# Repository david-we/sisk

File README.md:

# SiSK 

**THIS IS STILL WORK IN PROGRESS !**  

SiSK is a split keyboard with focus on standard staggered ISO Layout. it is an opportunity for those that do not want to jump on the ortholinear bandwagon, but still want to have the ergonomic advantages of a split keyboard. There will be a 60% version and a 65% Version of the PCB (which is already in the making). 

The plan is it starts as a base PCB which can then be easily used for DIY 3D-printed case designs. I am also planing to experiment with different case mounting techniques like top mount, sandwich mount, tray mount, gasket mount...

SiSK is meant as a wireless keyboard and my first prototype will use nice!nano v2 compatible Microcontroller boards and el cheapo 128x32 i2C displays for monitoring the battery...

## naming
**S**plit **I**SO **S**taggered **K**eyboard  
i know very ingenious :sweat_smile: but it was a very quick decision and AI created a logo that i liked, so its fine!

## features

- split
- ISO
- staggered
- wireless
- screw on wrist/palm wrest
- 128x32 OLED Display (I2C)
- 60% and 65% Version available
- first case will probably also use a foldable tenting solution (chinese mini Laptop stands)

### why?

I know there are similar keyboards out there, in fact there are also kits available that are in the same category. But still i was not satisfied with the existing solutions. Some where also hard to get in europe or had no ISO Layout. Another big point for me was the learning aspect, especially KiCAD and SMD soldering. AND i want a detachable solution for palm rests.

## pics

### history

last year i made this thing, which is kind of the predecessor of SiSK. But handwired and driven by a raspberry pi pico. It worked very well but the connector between the two halves sometimes looses contact. then i have to wobble around on the connector and it works again :P ... otherwise it worked flawless  

## next steps

waiting for PCBs :) 

## ideas for future

- ANSI layout

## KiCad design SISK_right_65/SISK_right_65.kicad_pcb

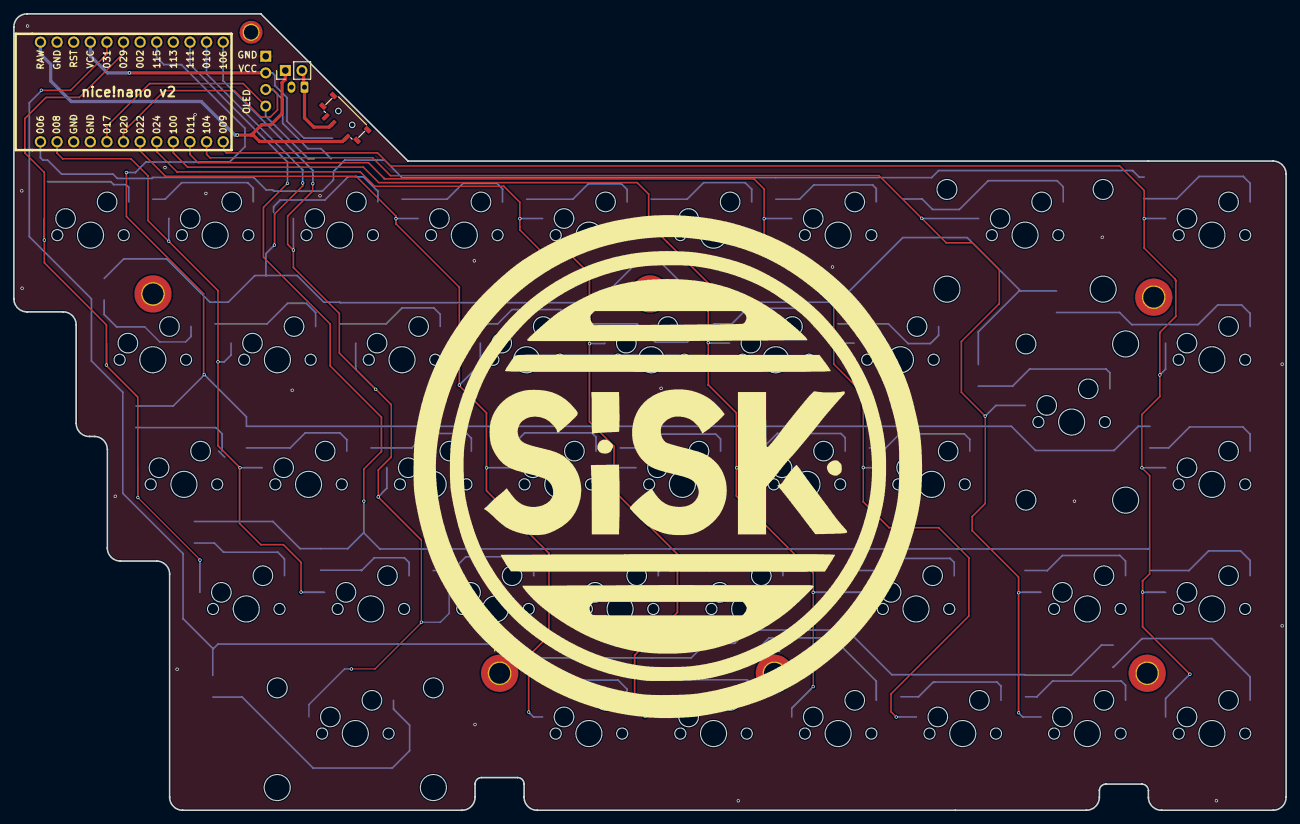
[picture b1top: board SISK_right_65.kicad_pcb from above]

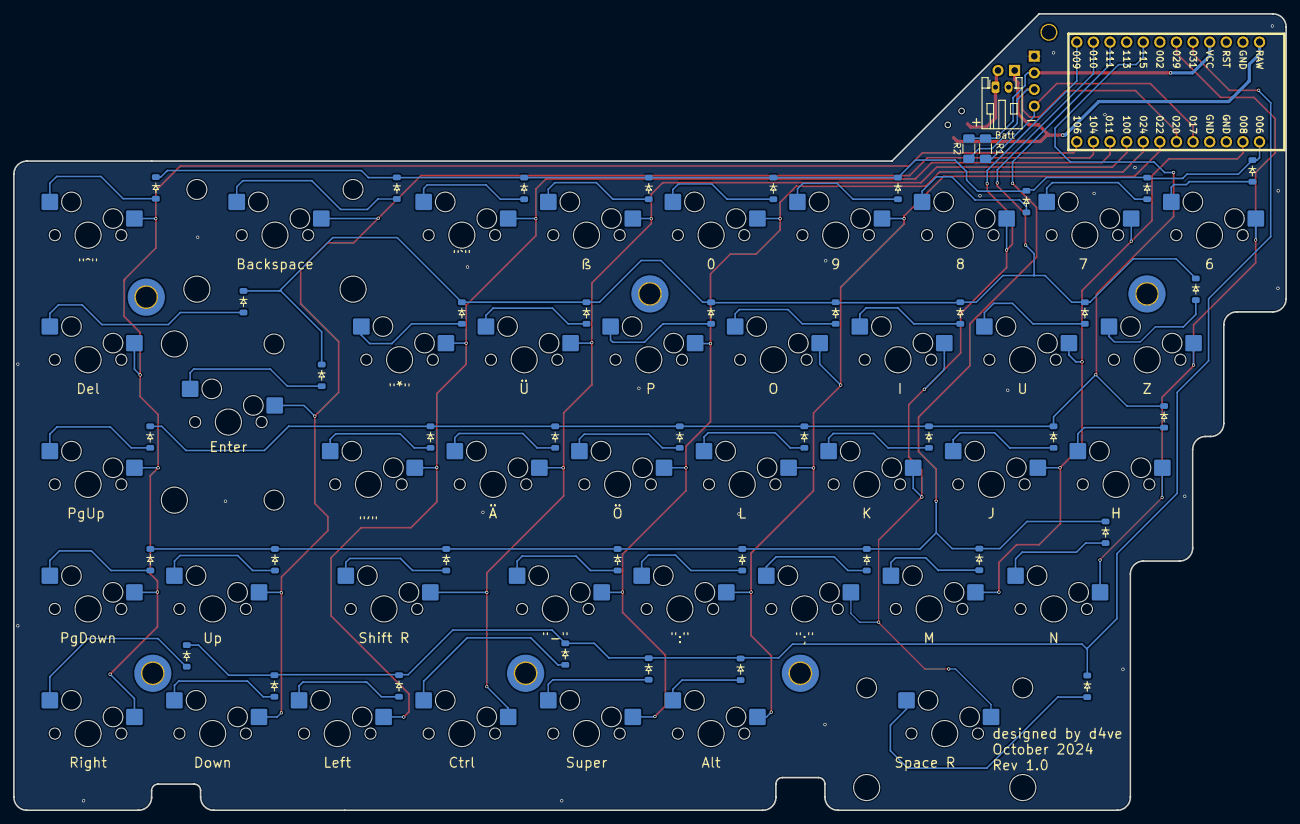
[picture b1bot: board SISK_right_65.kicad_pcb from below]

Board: 2 copper layers, 194.5 x 121.8 mm, 96 parts (85 on the bottom side), 61 nets.

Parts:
D1, D2, D3, D4, D5, D6, D7, D8, D9, D10, D11, D12, D13, D15, D16, D17, D18, D19, D21, D22, D23, D24, D25, D26, D27, D28, D29, D30, D31, D32, D33, D34, D35, D36, D37, D38, D39, D41, D42, D43, D44: D; Diode_SOD-123
H1, H2, H3, H4, H5, H7: M3; MountingHole_3.2mm_M3_ISO7380_Pad_TopBottom
H6: M2; MountingHole_2.2mm_M2_ISO7380_Pad_TopOnly
J1: OLED_128x32
J2: Batt; JST_PH_S2B-PH-K_1x02_P2.00mm_Horizontal
J3: SWITCH; PinHeader_1x02_P2.54mm_Vertical
R1, R2: 5K; R_1206_3216Metric_Pad1.30x1.75mm_HandSolder
SW1, SW2, SW3, SW4, SW5, SW6, SW7, SW9, SW10, SW11, SW12, SW13, SW14, SW15, SW16, SW18, SW19, SW20, SW21, SW22, SW23, SW24, SW25, SW26, SW27, SW28, SW29, SW30, SW31, SW33, SW34, SW36, SW37, SW38, SW39, SW40, SW41: SW_push; MX-Hotswap-1U
SW8: SW_push; MX-Hotswap-2U
SW17: SW_push; MX-Hotswap-ISO
SW32: SW_push; MX-Hotswap-1.75U
SW35: SW_push; MX-Hotswap-2.75U
SW-ONOFF-01: Switch_MSK12C02
U1: Nice_Nano_V2; nice_nano

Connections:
+3,3V: J1.2 (VCC), R1.1, R2.1, U1.21 (3.3v)
+BATT: J2.1, J3.2, SW-ONOFF-01.2 (B)
+VDC: J3.1, SW-ONOFF-01.1 (A), U1.24 (B+)
/COL0: SW1.1, SW10.1, SW19.1, SW27.1, U1.19 (20)
/COL1: SW2.1, SW11.1, SW20.1, SW28.1, U1.2 (0)
/COL2: SW3.1, SW12.1, SW21.1, SW29.1, SW35.1, U1.13 (10)
/COL3: SW4.1, SW13.1, SW22.1, SW30.1, SW36.1, U1.7 (4)
/COL4: SW5.1, SW14.1, SW23.1, SW31.1, SW37.1, U1.8 (5)
/COL5: SW6.1, SW15.1, SW24.1, SW32.1, SW38.1, U1.9 (6)
/COL6: SW7.1, SW16.1, SW25.1, SW39.1, U1.10 (7)
/COL7: SW8.1, SW17.1, SW33.1, SW40.1, U1.11 (8)
/COL8: SW9.1, SW18.1, SW26.1, SW34.1, SW41.1, U1.12 (9)
/ROW0: D1.1 (K), D6.1 (K), D11.1 (K), D16.1 (K), D21.1 (K), D26.1 (K), D31.1 (K), D36.1 (K), D41.1 (K), U1.1
/ROW1: D2.1 (K), D7.1 (K), D12.1 (K), D17.1 (K), D22.1 (K), D27.1 (K), D32.1 (K), D37.1 (K), D42.1 (K), U1.14 (16)
/ROW2: D3.1 (K), D13.1 (K), D18.1 (K), D23.1 (K), D28.1 (K), D33.1 (K), D38.1 (K), D43.1 (K), U1.17 (18)
/ROW3: D4.1 (K), D9.1 (K), D19.1 (K), D24.1 (K), D29.1 (K), D34.1 (K), D39.1 (K), D44.1 (K), U1.15 (14)
/ROW4: D5.1 (K), D8.1 (K), D10.1 (K), D15.1 (K), D25.1 (K), D30.1 (K), D35.1 (K), U1.20 (21)
/SCL: J1.3 (SCL), R2.2, U1.6 (3)
/SDA: J1.4 (SDA), R1.2, U1.5 (2)
GND: J1.1 (GND), J2.2, U1.3 (GND), U1.4 (GND), U1.23 (GND)
unnamed: D1.2 (A), SW9.2
unnamed: D2.2 (A), SW18.2
unnamed: D3.2 (A), SW26.2
unnamed: D4.2 (A), SW34.2
unnamed: D5.2 (A), SW41.2
unnamed: D6.2 (A), SW8.2
unnamed: D7.2 (A), SW17.2
unnamed: D8.2 (A), SW35.2
unnamed: D9.2 (A), SW33.2
unnamed: D10.2 (A), SW40.2
unnamed: D11.2 (A), SW7.2
unnamed: D12.2 (A), SW16.2
unnamed: D13.2 (A), SW25.2
unnamed: D15.2 (A), SW39.2
unnamed: D16.2 (A), SW6.2
unnamed: D17.2 (A), SW15.2
unnamed: D18.2 (A), SW24.2
unnamed: D19.2 (A), SW32.2
unnamed: D21.2 (A), SW5.2
unnamed: D22.2 (A), SW14.2
unnamed: D23.2 (A), SW23.2
unnamed: D24.2 (A), SW31.2
unnamed: D25.2 (A), SW38.2
unnamed: D26.2 (A), SW4.2
unnamed: D27.2 (A), SW13.2
unnamed: D28.2 (A), SW22.2
unnamed: D29.2 (A), SW30.2
unnamed: D30.2 (A), SW37.2
unnamed: D31.2 (A), SW3.2
unnamed: D32.2 (A), SW12.2
unnamed: D33.2 (A), SW21.2
unnamed: D34.2 (A), SW29.2
unnamed: D35.2 (A), SW36.2
unnamed: D36.2 (A), SW2.2
unnamed: D37.2 (A), SW11.2
unnamed: D38.2 (A), SW20.2
unnamed: D39.2 (A), SW28.2
unnamed: D41.2 (A), SW1.2
unnamed: D42.2 (A), SW10.2
unnamed: D43.2 (A), SW19.2
unnamed: D44.2 (A), SW27.2

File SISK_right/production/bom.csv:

Designator,Footprint,Quantity,Value,LCSC Part #
"D1, D10, D11, D12, D13, D15, D16, D17, D18, D19, D2, D21, D22, D23, D24, D25, D26, D27, D28, D29, D3, D30, D31, D32, D33, D34, D35, D36, D37, D38, D39, D4, D41, D42, D43, D44, D5, D6, D7, D8, D9",Diode_SOD-123,41,D,
J1,OLED_128x32,1,OLED_128x32,
J2,JST_PH_S2B-PH-K_1x02_P2.00mm_Horizontal,1,Battery Connector,
SW-ONOFF-01,Switch_MSK12C02,1,~,
SW1,Hotswap_MX_Plated_1.00u,1,"""6""",
SW10,Hotswap_MX_Plated_1.00u,1,"""Z""",
SW11,Hotswap_MX_Plated_1.00u,1,"""U""",
SW12,Hotswap_MX_Plated_1.00u,1,"""I""",
SW13,Hotswap_MX_Plated_1.00u,1,"""O""",
SW14,Hotswap_MX_Plated_1.00u,1,"""P""",
SW15,Hotswap_MX_Plated_1.00u,1,"""Ü""",
SW16,Hotswap_MX_Plated_1.00u,1,"""*""",
SW17,Hotswap_MX_Plated_ISOEnter,1,"""Enter""",
SW18,Hotswap_MX_Plated_1.00u,1,"""Del""",
SW19,Hotswap_MX_Plated_1.00u,1,"""H""",
SW2,Hotswap_MX_Plated_1.00u,1,"""7""",
SW20,Hotswap_MX_Plated_1.00u,1,"""J""",
SW21,Hotswap_MX_Plated_1.00u,1,"""K""",
SW22,Hotswap_MX_Plated_1.00u,1,"""L""",
SW23,Hotswap_MX_Plated_1.00u,1,"""Ö""",
SW24,Hotswap_MX_Plated_1.00u,1,"""Ä""",
SW25,Hotswap_MX_Plated_1.00u,1,"""'""",
SW26,Hotswap_MX_Plated_1.00u,1,"""PGUP""",
SW27,Hotswap_MX_Plated_1.00u,1,"""N""",
SW28,Hotswap_MX_Plated_1.00u,1,"""M""",
SW29,Hotswap_MX_Plated_1.00u,1,""";""",
SW3,Hotswap_MX_Plated_1.00u,1,"""8""",
SW30,Hotswap_MX_Plated_1.00u,1,""":""",
SW31,Hotswap_MX_Plated_1.00u,1,"""-""",
SW32,Hotswap_MX_Plated_1.75u,1,"""shift_R""",
SW33,Hotswap_MX_Plated_1.00u,1,"""UP""",
SW34,Hotswap_MX_Plated_1.00u,1,"""PGDOWN""",
SW35,Hotswap_MX_Plated_2.75u,1,"""SPACE_R""",
SW36,Hotswap_MX_Plated_1.00u,1,"""Alt""",
SW37,Hotswap_MX_Plated_1.00u,1,FN,
SW38,Hotswap_MX_Plated_1.00u,1,"""Ctrl""",
SW39,Hotswap_MX_Plated_1.00u,1,"""Left""",
SW4,Hotswap_MX_Plated_1.00u,1,"""9""",
SW40,Hotswap_MX_Plated_1.00u,1,"""Down""",
SW41,Hotswap_MX_Plated_1.00u,1,"""Right""",
SW5,Hotswap_MX_Plated_1.00u,1,"""0""",
SW6,Hotswap_MX_Plated_1.00u,1,"""ß""",
SW7,Hotswap_MX_Plated_1.00u,1,"""`""",
SW8,Hotswap_MX_Plated_2.00u,1,"""Backspace""",
SW9,Hotswap_MX_Plated_1.00u,1,"""^""",
U1,Nice_Nano_V2,1,Nice_Nano_V2,

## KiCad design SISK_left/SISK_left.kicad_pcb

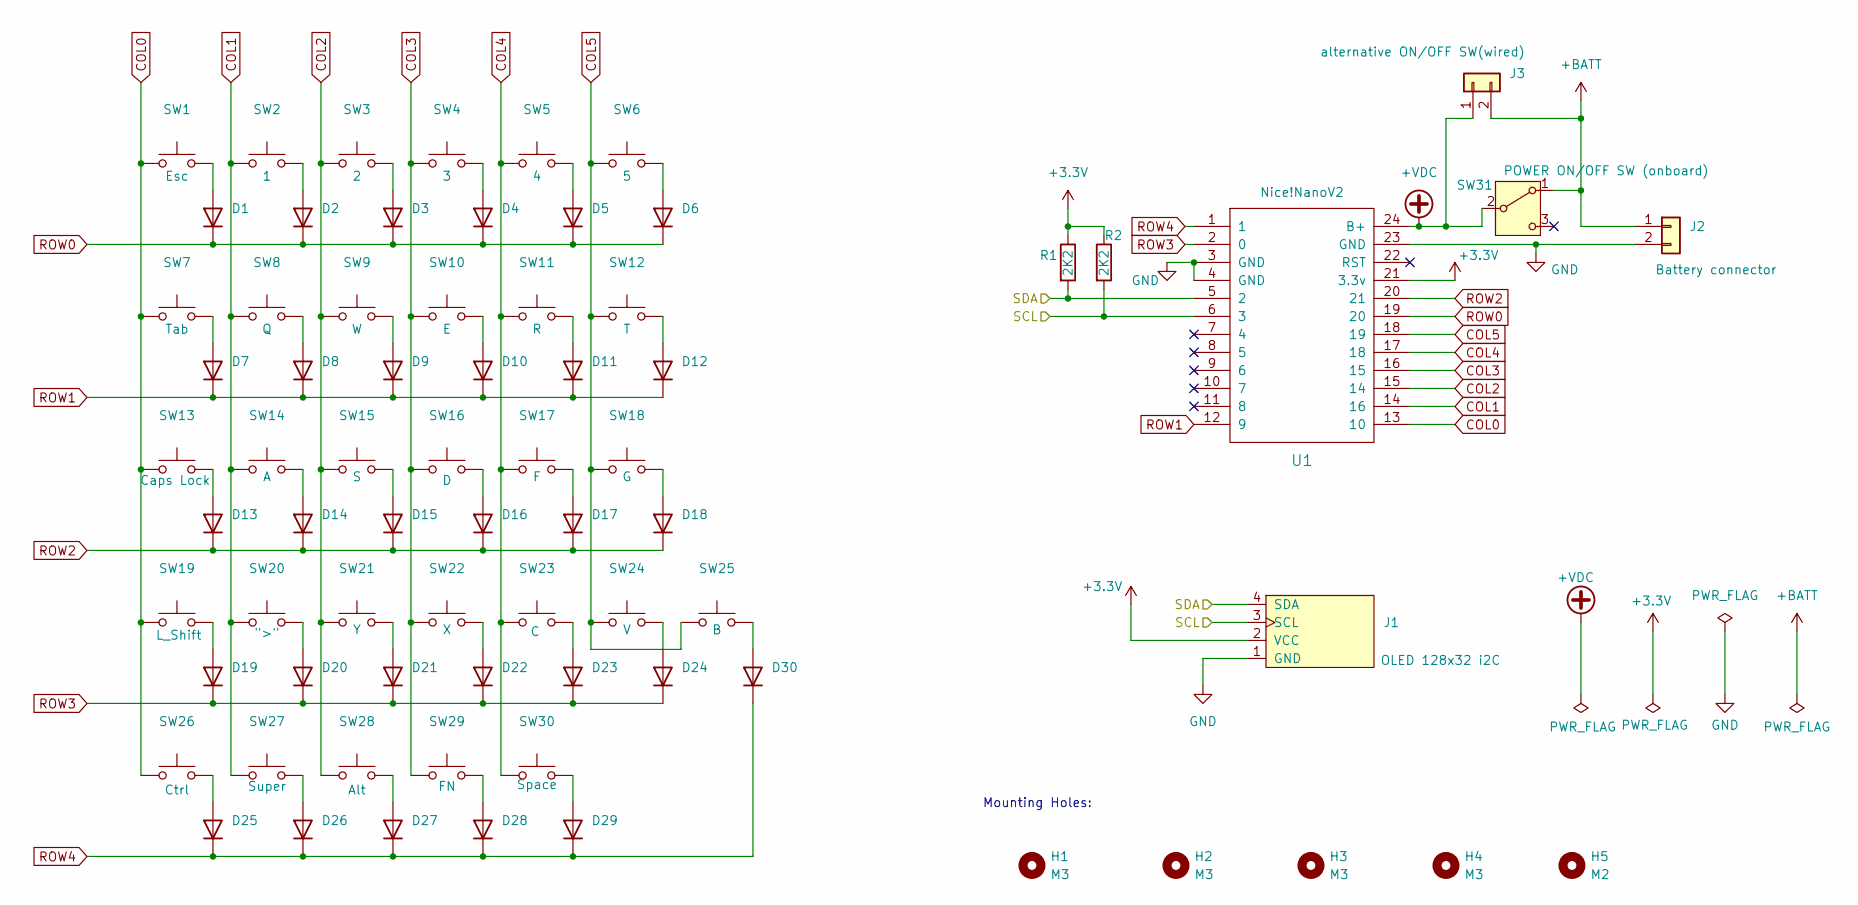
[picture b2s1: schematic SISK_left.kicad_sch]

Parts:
D1, D2, D3, D4, D5, D6, D7, D8, D9, D10, D11, D12, D13, D14, D15, D16, D17, D18, D19, D20, D21, D22, D23, D24, D25, D26, D27, D28, D29, D30: 1n4148; Diode_SOD-123; MPN 1N4148W
H1, H2, H3, H4: M3; MountingHole_3.2mm_M3_ISO7380_Pad_TopBottom
H5: M2; MountingHole_2.2mm_M2_ISO7380_Pad_TopOnly
J1: OLED_128x32; MPN OLED 128x32 i2C
J2: BAT; JST_PH_S2B-PH-K_1x02_P2.00mm_Horizontal; MPN S2B-PH-K-S(LF)(SN)
J3: CONN_ALT; PinHeader_1x02_P2.54mm_Vertical; MPN not known yet
R1, R2: 2K2; R_1206_3216Metric_Pad1.30x1.75mm_HandSolder; MPN RC1206JR-072K2L
SW1, SW2, SW3, SW4, SW5, SW6, SW8, SW9, SW10, SW11, SW12, SW14, SW15, SW16, SW17, SW18, SW20, SW21, SW22, SW23, SW24, SW25: SW_push; MX-Hotswap-1U; MPN CPG151101S11
SW7: SW_push; MX-Hotswap-1.5U; MPN CPG151101S11
SW13: SW_push; MX-Hotswap-1.75U; MPN CPG151101S11
SW19, SW26, SW27, SW28, SW29: SW_push; MX-Hotswap-1.25U; MPN CPG151101S11
SW30: SW_push; MX-Hotswap-2.25U; MPN CPG151101S11
SW31: SW_SPDT; Switch_MSK12C02; MPN MSK12C01
U1: Nice_Nano_V2; nice_nano; MPN nice!nano v2 or compatible

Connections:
+3.3V: J1.2 (VCC), R1.1, R2.1, U1.21 (3.3v)
+BATT: J2.1, J3.2, SW31.1 (A)
+VDC: J3.1, SW31.2 (B), U1.24 (B+)
/SCL: J1.3 (SCL), R2.2, U1.6 (3)
/SDA: J1.4 (SDA), R1.2, U1.5 (2)
COL0: SW1.1, SW7.1, SW13.1, SW19.1, SW26.1, U1.13 (10)
COL1: SW2.1, SW8.1, SW14.1, SW20.1, SW27.1, U1.14 (16)
COL2: SW3.1, SW9.1, SW15.1, SW21.1, SW28.1, U1.15 (14)
COL3: SW4.1, SW10.1, SW16.1, SW22.1, SW29.1, U1.16 (15)
COL4: SW5.1, SW11.1, SW17.1, SW23.1, SW30.1, U1.17 (18)
COL5: SW6.1, SW12.1, SW18.1, SW24.1, SW25.1, U1.18 (19)
GND: J1.1 (GND), J2.2, U1.3 (GND), U1.4 (GND), U1.23 (GND)
unnamed: D1.2 (A), SW1.2
unnamed: D2.2 (A), SW2.2
unnamed: D3.2 (A), SW3.2
unnamed: D4.2 (A), SW4.2
unnamed: D5.2 (A), SW5.2
unnamed: D6.2 (A), SW6.2
unnamed: D7.2 (A), SW7.2
unnamed: D8.2 (A), SW8.2
unnamed: D9.2 (A), SW9.2
unnamed: D10.2 (A), SW10.2
unnamed: D11.2 (A), SW11.2
unnamed: D12.2 (A), SW12.2
unnamed: D13.2 (A), SW13.2
unnamed: D14.2 (A), SW14.2
unnamed: D15.2 (A), SW15.2
unnamed: D16.2 (A), SW16.2
unnamed: D17.2 (A), SW17.2
unnamed: D18.2 (A), SW18.2
unnamed: D19.2 (A), SW19.2
unnamed: D20.2 (A), SW20.2
unnamed: D21.2 (A), SW21.2
unnamed: D22.2 (A), SW22.2
unnamed: D23.2 (A), SW23.2
unnamed: D24.2 (A), SW24.2
unnamed: D25.2 (A), SW26.2
unnamed: D26.2 (A), SW27.2
unnamed: D27.2 (A), SW28.2
unnamed: D28.2 (A), SW29.2
unnamed: D29.2 (A), SW30.2
unnamed: D30.2 (A), SW25.2
ROW0: D1.1 (K), D2.1 (K), D3.1 (K), D4.1 (K), D5.1 (K), D6.1 (K), U1.19 (20)
ROW1: D7.1 (K), D8.1 (K), D9.1 (K), D10.1 (K), D11.1 (K), D12.1 (K), U1.12 (9)
ROW2: D13.1 (K), D14.1 (K), D15.1 (K), D16.1 (K), D17.1 (K), D18.1 (K), U1.20 (21)
ROW3: D19.1 (K), D20.1 (K), D21.1 (K), D22.1 (K), D23.1 (K), D24.1 (K), U1.2 (0)
ROW4: D25.1 (K), D26.1 (K), D27.1 (K), D28.1 (K), D29.1 (K), D30.1 (K), U1.1

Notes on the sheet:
Mounting Holes:

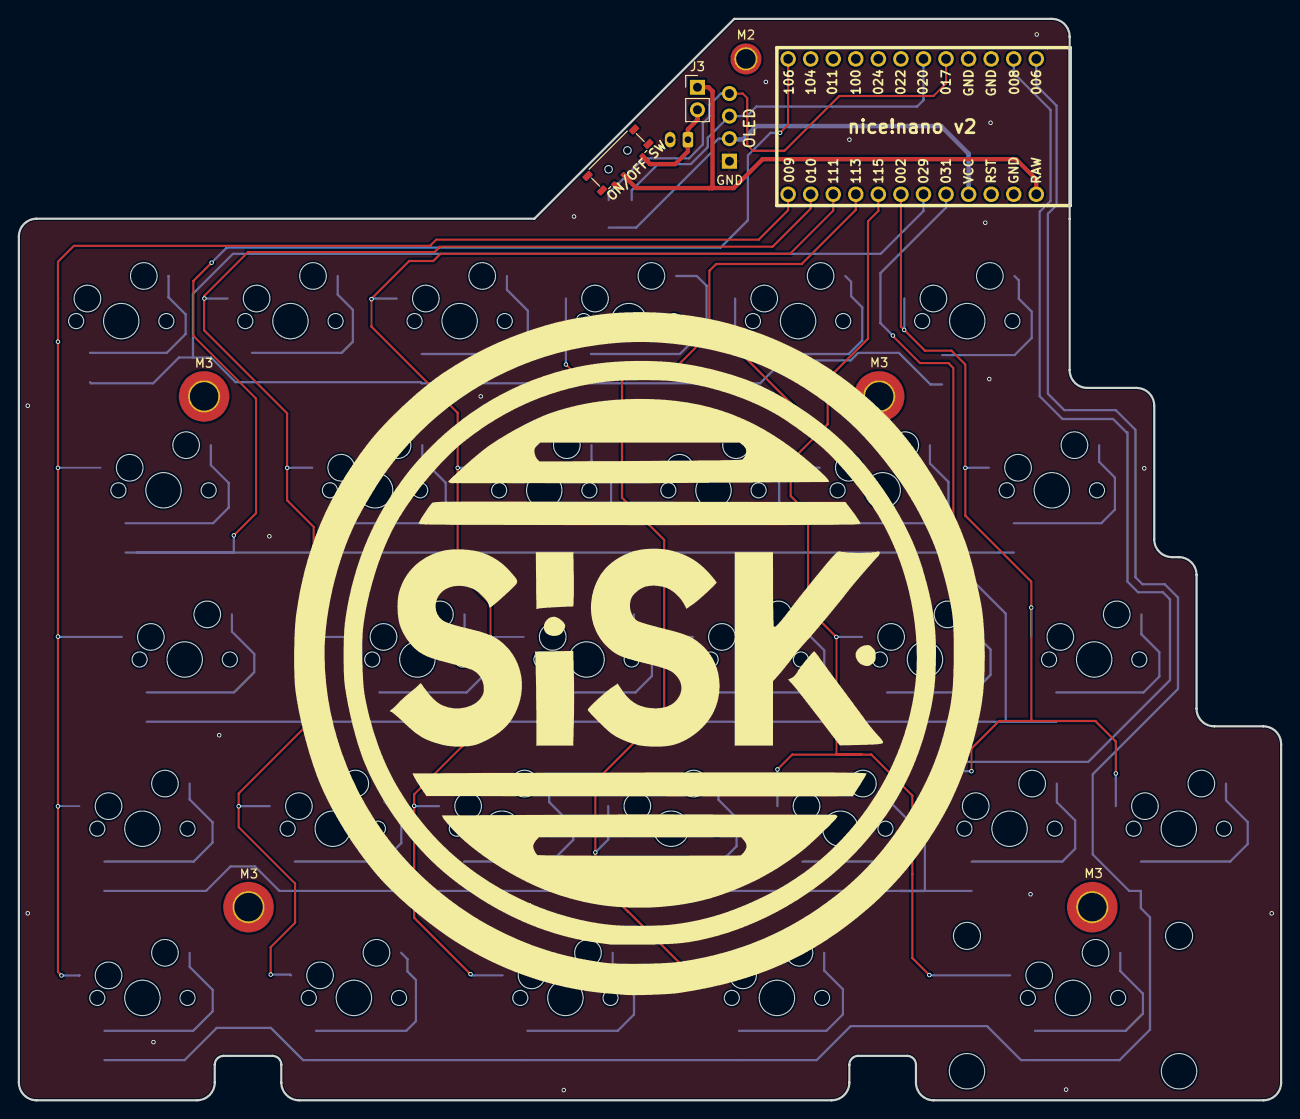
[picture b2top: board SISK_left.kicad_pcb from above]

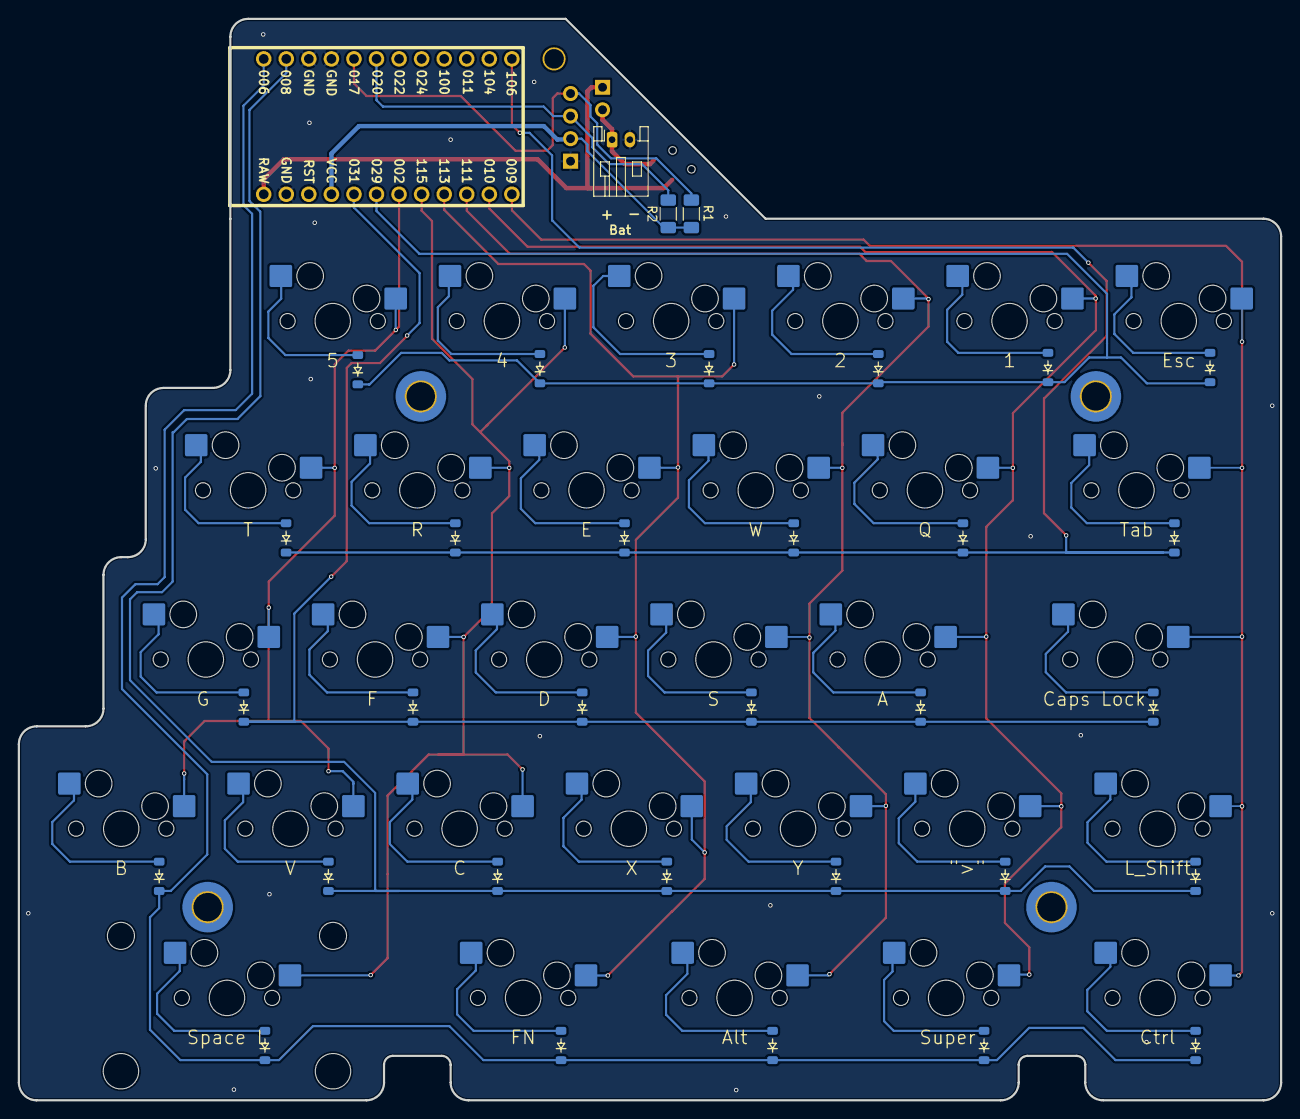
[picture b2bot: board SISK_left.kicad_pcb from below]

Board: 2 copper layers, 142.1 x 121.8 mm, 72 parts (63 on the bottom side), 47 nets.

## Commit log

2024-10-03 add gitignore file
2024-10-03 added files
2024-10-03 added pics
2024-10-03 Rename 2024-10-04 00_28_24-3D Viewer.png to left_sisk_3d.png
2024-10-03 Rename 2024-10-04 00_33_59-3D Viewer.png to right_sisk_3d.png
2024-10-07 changes after first review
2024-10-08 changed nice nano footprint
2024-10-08 Update README.md
    added routing pics
2024-10-09 added some text and alternative header for Power Switch
2024-10-11 changed file structure, added new project for 60%, changed main footprints for hotswap sockets
2024-10-11 fixed schematics, added optional pullup resistors
2024-10-12 fixed some issues
2024-10-13 fixed most of issues, updated 60% version
2024-10-13 improved the whole mounting hole situation
2024-10-13 last changes on silkscreen before manufaturing
2024-10-13 add logo with transparent background
2024-10-13 add pics
2024-10-13 add test to README
